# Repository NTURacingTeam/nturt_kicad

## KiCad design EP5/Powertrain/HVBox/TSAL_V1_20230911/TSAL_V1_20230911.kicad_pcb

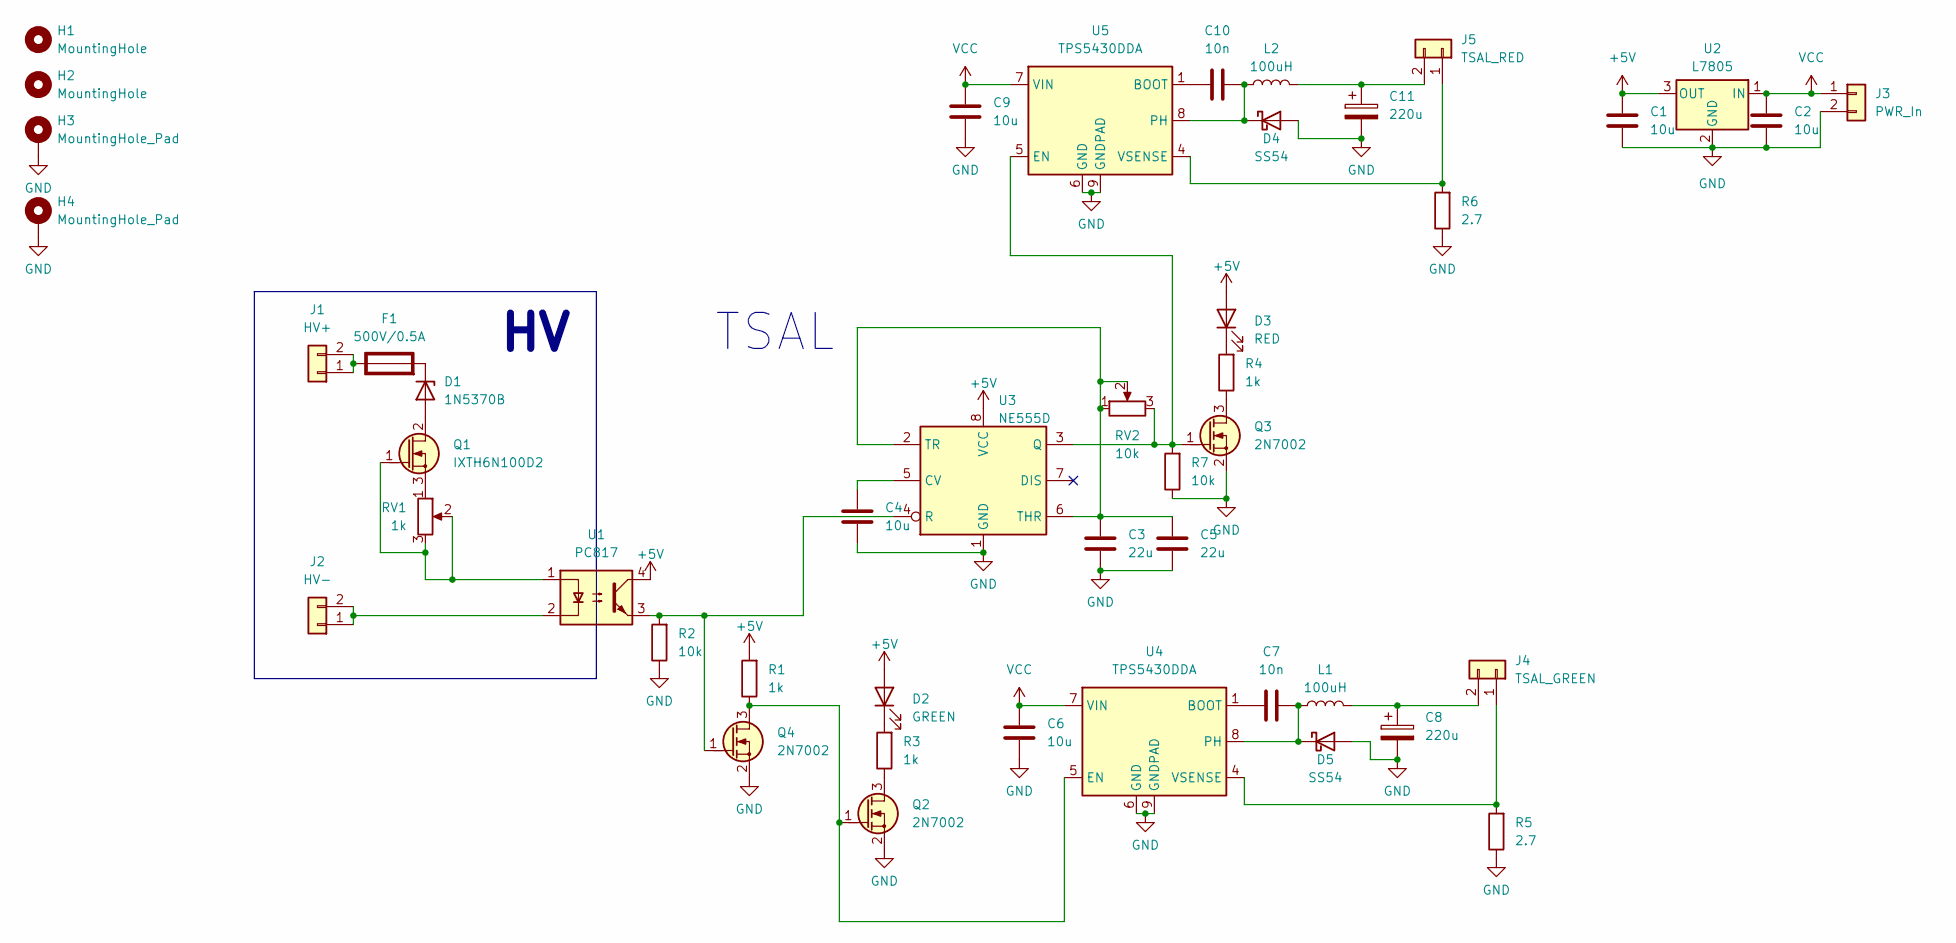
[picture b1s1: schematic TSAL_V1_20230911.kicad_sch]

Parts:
C1, C2, C4, C6, C9: 10u; C_0805_2012Metric_Pad1.18x1.45mm_HandSolder
C3, C5: 22u; C_0805_2012Metric_Pad1.18x1.45mm_HandSolder
C7, C10: 10n; C_0805_2012Metric_Pad1.18x1.45mm_HandSolder
C8, C11: 220u; CP_Elec_8x10.5
D1: 1N5370B; D_P600_R-6_P15.24mm_Horizontal_Zener
D2: GREEN; LED_0805_2012Metric
D3: RED; LED_0805_2012Metric
D4, D5: SS54; D_SMA
F1: 500V/0.5A; 65600001009; Rating W
H1, H2: MountingHole; MountingHole_4.3mm_M4_DIN965
H3, H4: MountingHole_Pad; MountingHole_4.3mm_M4_DIN965_Pad_TopBottom
J1: HV+; DF33C2P33DSA24
J2: HV-; DF33C2P33DSA24
J3: PWR_In; JST_XH_B2B-XH-A_1x02_P2.50mm_Vertical
J4: TSAL_GREEN; JST_XH_B2B-XH-A_1x02_P2.50mm_Vertical
J5: TSAL_RED; JST_XH_B2B-XH-A_1x02_P2.50mm_Vertical
L1, L2: 100uH; L_Sunlord_MWSA1206S-101
Q1: IXTH6N100D2; TO-247-3_Vertical
Q2, Q3, Q4: 2N7002; SOT-23
R1, R3, R4: 1k; R_0805_2012Metric_Pad1.20x1.40mm_HandSolder
R2, R7: 10k; R_0805_2012Metric_Pad1.20x1.40mm_HandSolder
R5, R6: 2.7; R_2512_6332Metric
RV1: 1k; Potentiometer_Bourns_3386C_Horizontal
RV2: 10k; Potentiometer_Bourns_3386C_Horizontal
U1: PC817; SOP-4_3.8x4.1mm_P2.54mm
U2: L7805; TO-252-2
U3: NE555D; SOIC-8_3.9x4.9mm_P1.27mm
U4, U5: TPS5430DDA; TI_SO-PowerPAD-8_ThermalVias

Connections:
+5V: C1.1, D2.2 (A), D3.2 (A), R1.2, U1.4, U2.3 (OUT), U3.8 (VCC)
GND: C1.2, C2.2, C3.2, C4.2, C5.2, C6.2, C8.2, C9.2, C11.2, D4.2 (A), D5.2 (A), H3.1, H4.1, J3.2, Q2.2 (S), Q3.2 (S), Q4.2 (S), R2.1, R5.1, R6.1, R7.1, U2.2 (GND), U3.1 (GND), U4.6 (GND), U4.9 (GNDPAD), U5.6 (GND), U5.9 (GNDPAD)
unnamed: D1.2 (A), Q1.2 (D)
unnamed: D1.1 (K), F1.2 (-)
unnamed: D2.1 (K), R3.2
unnamed: D3.1 (K), R4.2
unnamed: C10.2, D4.1 (K), L2.1, U5.8 (PH)
unnamed: C7.2, D5.1 (K), L1.1, U4.8 (PH)
unnamed: F1.1 (+), J1.1, J1.2
unnamed: J2.1, J2.2, U1.2
unnamed: J4.1, R5.2, U4.4 (VSENSE)
unnamed: C8.1, J4.2, L1.2
unnamed: J5.1, R6.2, U5.4 (VSENSE)
unnamed: C11.1, J5.2, L2.2
unnamed: Q1.1 (G), RV1.2, RV1.3, U1.1
unnamed: Q1.3 (S), RV1.1
unnamed: Q2.3 (D), R3.1
unnamed: Q2.1 (G), Q4.3 (D), R1.1, U4.5 (EN)
unnamed: Q3.3 (D), R4.1
unnamed: Q3.1 (G), R7.2, RV2.3, U3.3 (Q), U5.5 (EN)
unnamed: Q4.1 (G), R2.2, U1.3, U3.4 (R)
unnamed: C4.1, U3.5 (CV)
unnamed: C3.1, C5.1, RV2.1, RV2.2, U3.2 (TR), U3.6 (THR)
unnamed: C7.1, U4.1 (BOOT)
unnamed: C10.1, U5.1 (BOOT)
VCC: C2.1, C6.1, C9.1, J3.1, U2.1 (IN), U4.7 (VIN), U5.7 (VIN)

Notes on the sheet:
TSAL

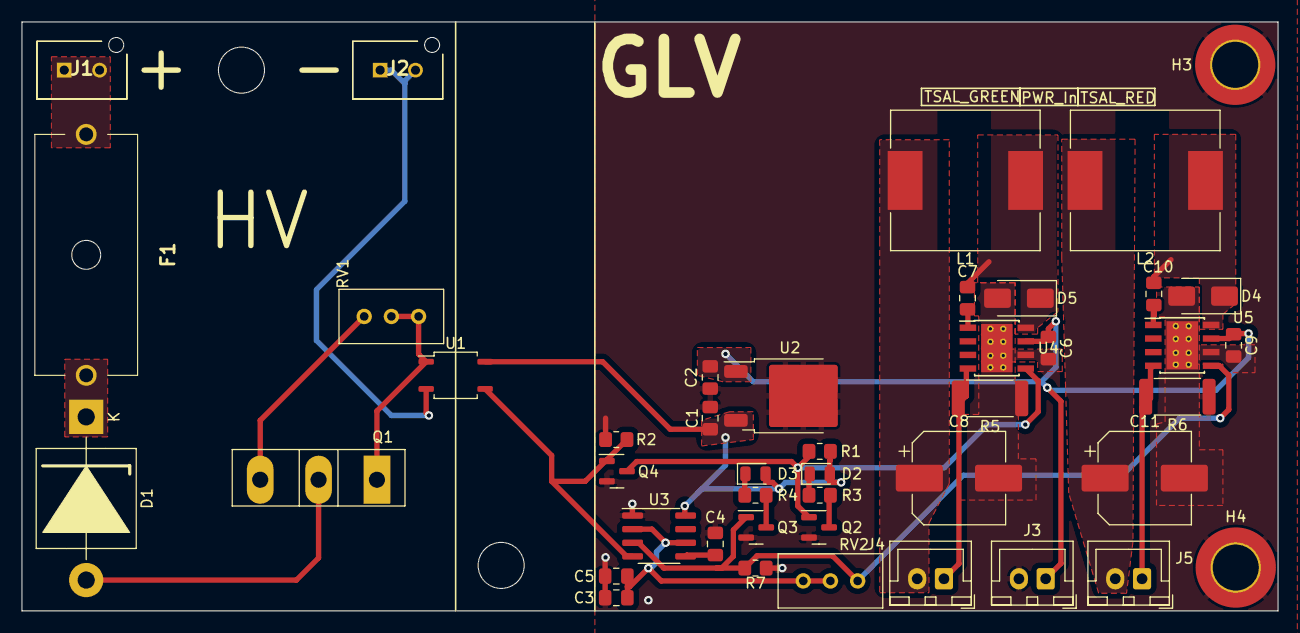
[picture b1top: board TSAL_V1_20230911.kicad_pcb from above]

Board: 2 copper layers, 117.3 x 55.0 mm, 46 parts (0 on the bottom side), 26 nets.

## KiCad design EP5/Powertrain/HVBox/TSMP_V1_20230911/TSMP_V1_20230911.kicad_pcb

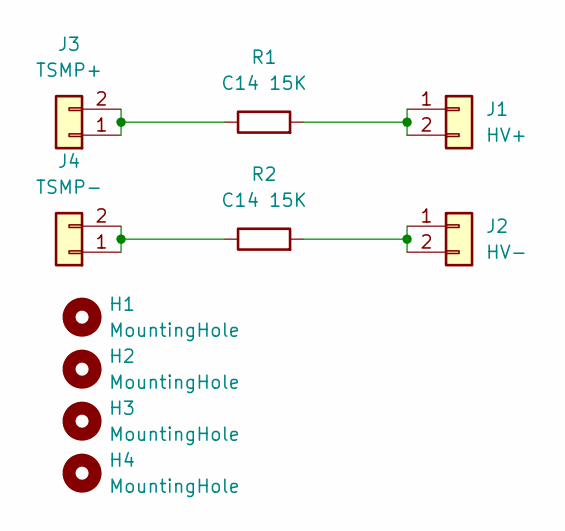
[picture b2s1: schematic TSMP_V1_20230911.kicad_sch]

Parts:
H1, H2, H3, H4: MountingHole; MountingHole_4.3mm_M4_DIN965
J1: HV+; DF33C2P33DSA24
J2: HV-; DF33C2P33DSA24
J3: TSMP+; DF33C2P33DSA24
J4: TSMP-; DF33C2P33DSA24
R1, R2: C14 15K; R_Axial_Power_L60.0mm_W14.0mm_P71.12mm

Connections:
unnamed: J1.1, J1.2, R1.2
unnamed: J2.1, J2.2, R2.2
unnamed: J3.1, J3.2, R1.1
unnamed: J4.1, J4.2, R2.1

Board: 2 copper layers, 10 parts (0 on the bottom side), 4 nets, no tracks yet.

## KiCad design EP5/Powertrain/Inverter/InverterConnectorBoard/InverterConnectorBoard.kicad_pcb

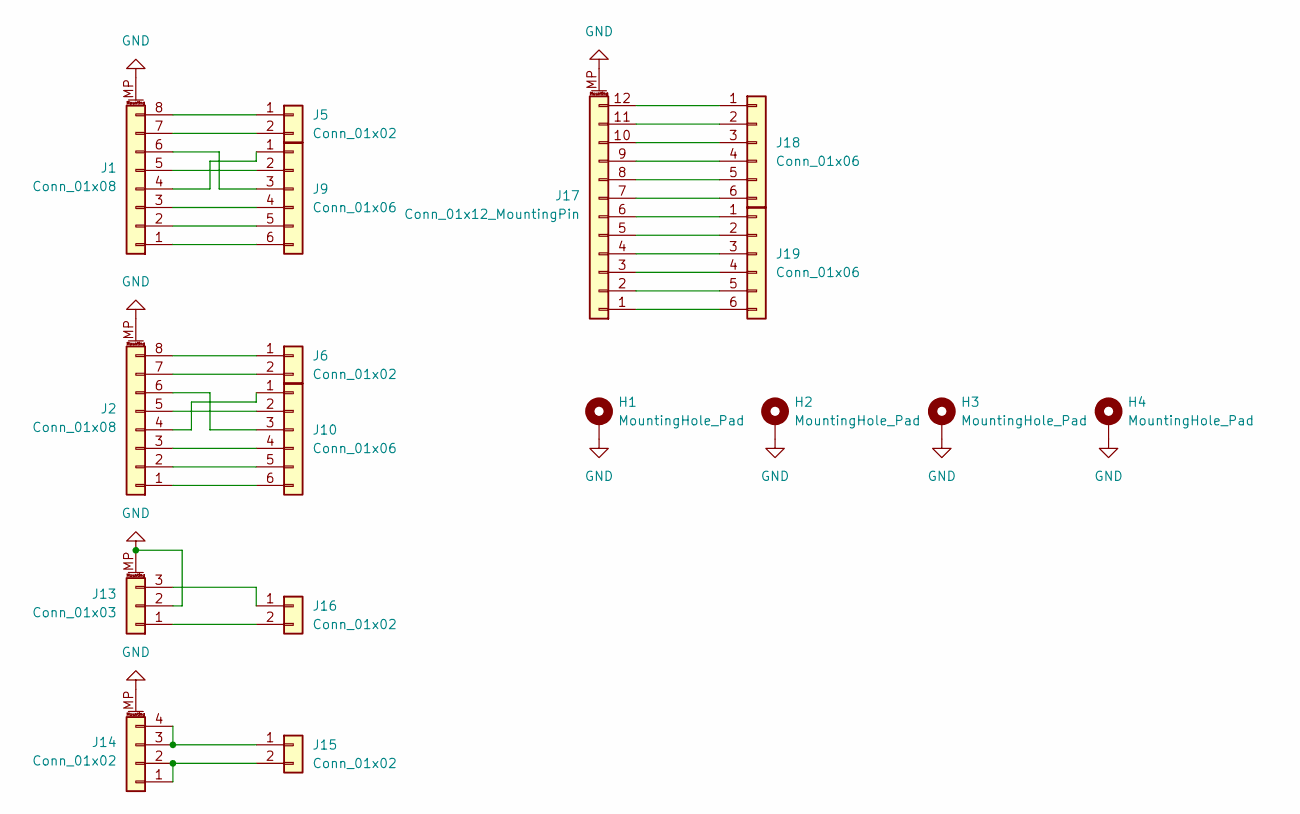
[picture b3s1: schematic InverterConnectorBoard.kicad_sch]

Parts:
H1, H2, H3, H4: MountingHole_Pad; MountingHole_4.3mm_M4_DIN965_Pad_TopBottom
J1, J2: Conn_01x08; M8 8P w Ground
J5, J6, J15, J16: Conn_01x02; JST_XH_B2B-XH-A_1x02_P2.50mm_Vertical
J9, J10, J18, J19: Conn_01x06; JST_XH_B6B-XH-A_1x06_P2.50mm_Vertical
J13: Conn_01x03; M8 3P w Ground
J14: Conn_01x02; M8 2P 4P w Ground
J17: Conn_01x12_MountingPin; M12 12P w Ground

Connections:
GND: H1.1, H2.1, H3.1, H4.1, J1.MP (MountPin), J2.MP (MountPin), J13.2, J13.MP (MountPin), J14.MP (MountPin), J17.MP (MountPin)
unnamed: J1.1, J9.6
unnamed: J1.2, J9.5
unnamed: J1.3, J9.4
unnamed: J1.4, J9.1
unnamed: J1.5, J9.2
unnamed: J1.6, J9.3
unnamed: J1.7, J5.2
unnamed: J1.8, J5.1
unnamed: J2.7, J6.2
unnamed: J2.8, J6.1
unnamed: J2.4, J10.1
unnamed: J2.5, J10.2
unnamed: J2.6, J10.3
unnamed: J2.3, J10.4
unnamed: J2.2, J10.5
unnamed: J2.1, J10.6
unnamed: J13.1, J16.2
unnamed: J13.3, J16.1
unnamed: J14.1, J14.2, J15.2
unnamed: J14.3, J14.4, J15.1
unnamed: J17.1, J19.6
unnamed: J17.2, J19.5
unnamed: J17.3, J19.4
unnamed: J17.4, J19.3
unnamed: J17.5, J19.2
unnamed: J17.6, J19.1
unnamed: J17.7, J18.6
unnamed: J17.8, J18.5
unnamed: J17.9, J18.4
unnamed: J17.10, J18.3
unnamed: J17.11, J18.2
unnamed: J17.12, J18.1

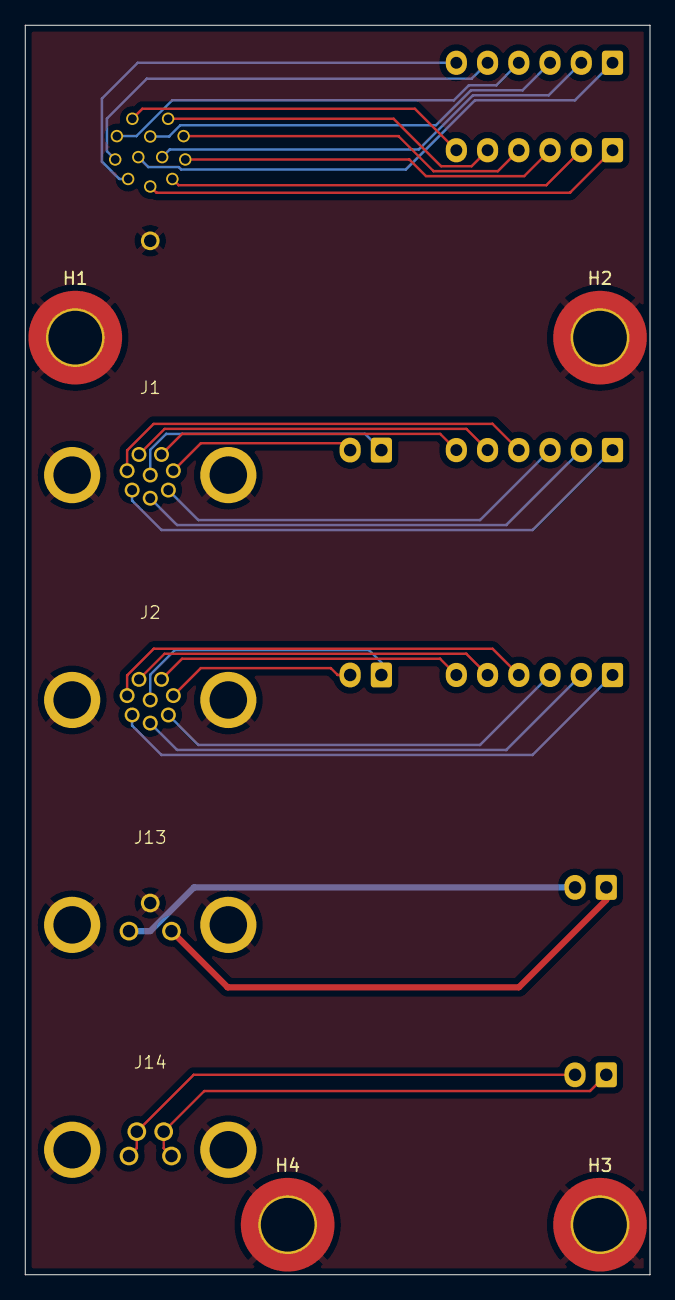
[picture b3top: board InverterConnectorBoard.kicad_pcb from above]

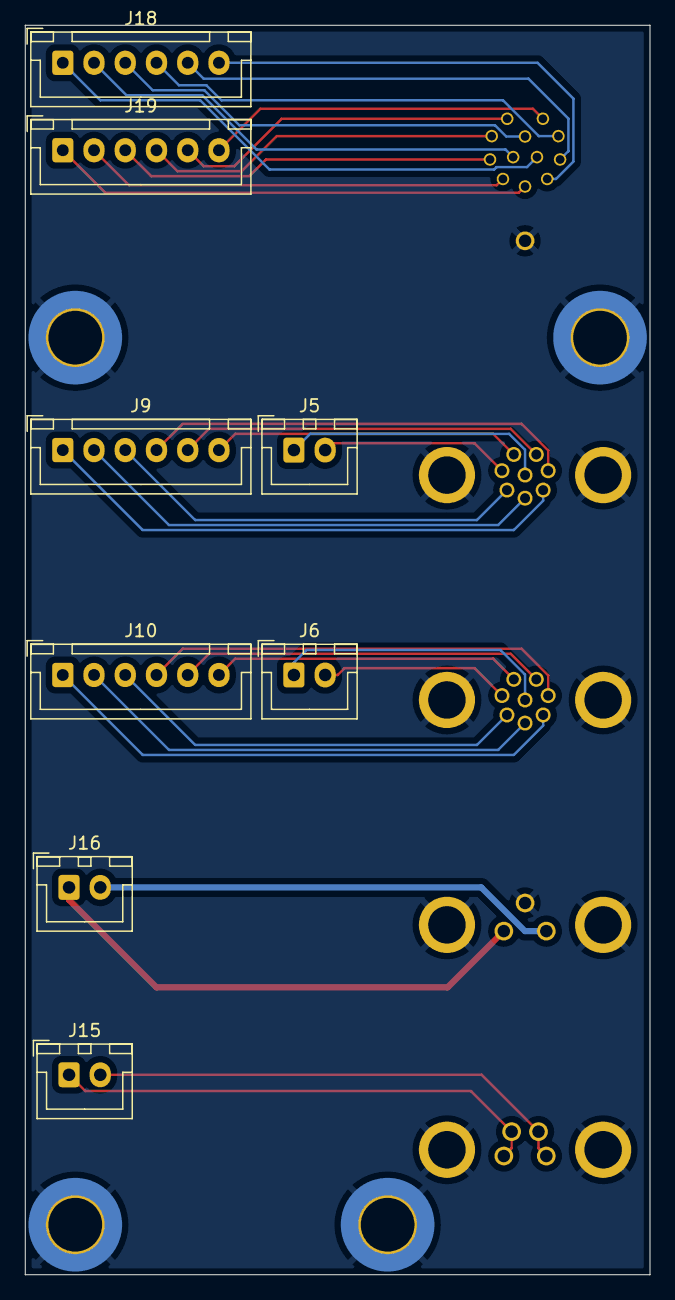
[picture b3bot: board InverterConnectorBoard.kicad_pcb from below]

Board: 2 copper layers, 50.0 x 100.0 mm, 17 parts (8 on the bottom side), 33 nets.

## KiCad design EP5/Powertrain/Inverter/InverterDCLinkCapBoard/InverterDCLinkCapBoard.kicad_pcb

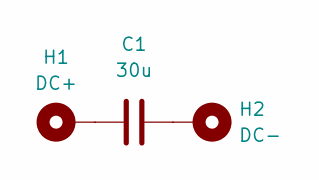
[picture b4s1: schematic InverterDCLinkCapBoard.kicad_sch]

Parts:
C1: 30u; C4AQ-M_WJ
H1: DC+; MountingHole_5.5mm_Pad_Via
H2: DC-; MountingHole_5.5mm_Pad_Via

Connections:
unnamed: C1.1, H1.1
unnamed: C1.2, H2.1

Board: 2 copper layers, 3 parts (0 on the bottom side), 2 nets, no tracks yet.

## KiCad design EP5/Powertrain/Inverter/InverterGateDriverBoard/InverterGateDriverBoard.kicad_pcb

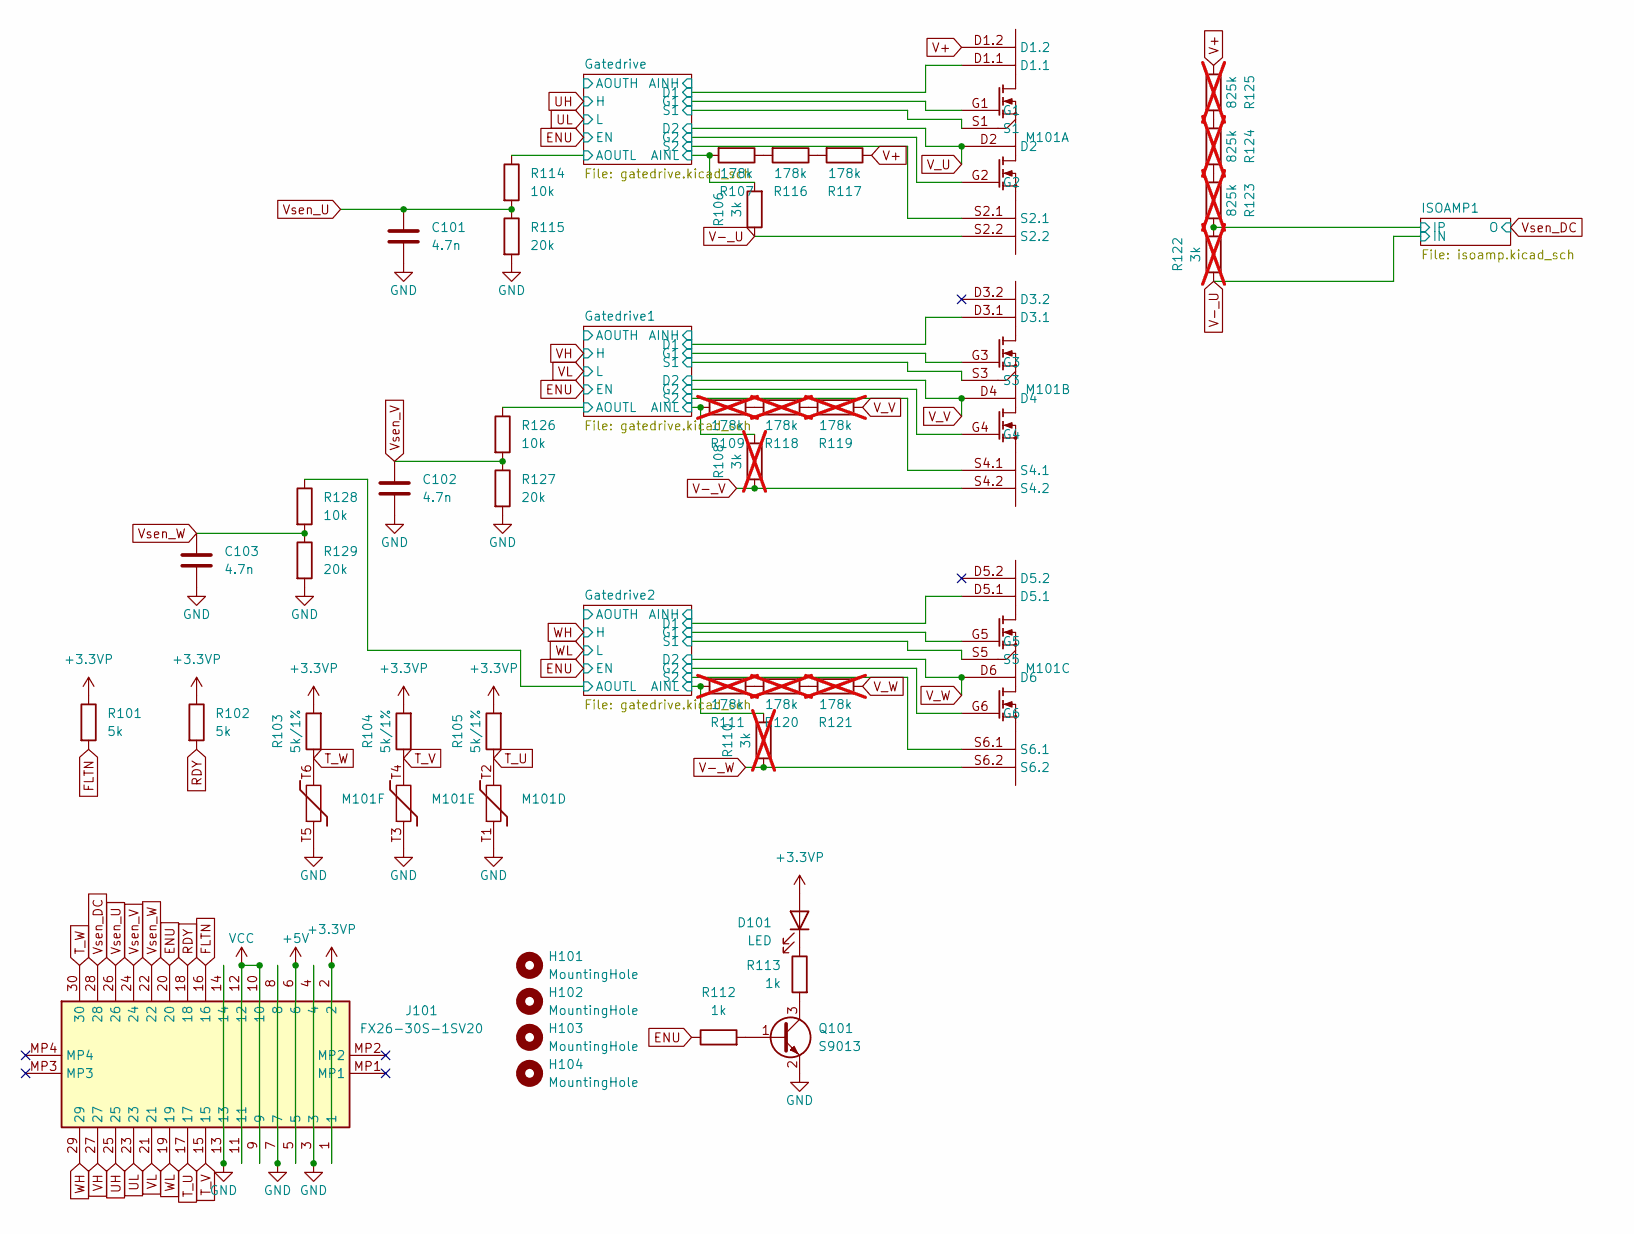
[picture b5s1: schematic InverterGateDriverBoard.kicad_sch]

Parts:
C101, C102, C103: 4.7n; C_0603_1608Metric
D101: LED; LED_0603_1608Metric
H101, H102, H103, H104: MountingHole; MountingHole_4mm
J101: FX26-30S-1SV20; FX2630S1SV20; Mouser Part Number 798-FX2630S1SV20
M101: InverterSiCModule
Q101: S9013; SOT-23-3
R101, R102: 5k; R_0603_1608Metric
R103, R104, R105: 5k/1%; R_0603_1608Metric
R106: 3k; R_1206_3216Metric
R107, R116, R117: 178k; R_1206_3216Metric
R108, R110, R122: 3k; R_1206_3216Metric; not fitted
R109, R111, R118, R119, R120, R121: 178k; R_1206_3216Metric; not fitted
R112, R113: 1k; R_0603_1608Metric
R114, R126, R128: 10k; R_0603_1608Metric
R115, R127, R129: 20k; R_0603_1608Metric
R123, R124, R125: 825k; R_1206_3216Metric; not fitted

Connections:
+3.3VP: D101.2 (A), J101.1, J101.2, R101.1, R102.1, R103.2, R104.2, R105.2; also elsewhere on the board
+5V: J101.5, J101.6; also elsewhere on the board
/Gatedrive1/AINL: R108.2, R109.2; also elsewhere on the board
/Gatedrive1/AOUTL: R126.1; also elsewhere on the board
/Gatedrive1/D1: M101.D3.1; also elsewhere on the board
/Gatedrive1/G1: M101.G3; also elsewhere on the board
/Gatedrive1/G2: M101.G4; also elsewhere on the board
/Gatedrive1/S1: M101.S3; also elsewhere on the board
/Gatedrive1/S2: M101.S4.1; also elsewhere on the board
/Gatedrive2/AINL: R110.2, R111.2; also elsewhere on the board
/Gatedrive2/AOUTL: R128.1; also elsewhere on the board
/Gatedrive2/D1: M101.D5.1; also elsewhere on the board
/Gatedrive2/G1: M101.G5; also elsewhere on the board
/Gatedrive2/G2: M101.G6; also elsewhere on the board
/Gatedrive2/S1: M101.S5; also elsewhere on the board
/Gatedrive2/S2: M101.S6.1; also elsewhere on the board
/Gatedrive/AINL: R106.2, R107.2; also elsewhere on the board
/Gatedrive/AOUTL: R114.1; also elsewhere on the board
/Gatedrive/D1: M101.D1.1; also elsewhere on the board
/Gatedrive/G1: M101.G1; also elsewhere on the board
/Gatedrive/G2: M101.G2; also elsewhere on the board
/Gatedrive/S1: M101.S1; also elsewhere on the board
/Gatedrive/S2: M101.S2.1; also elsewhere on the board
/ISOAMP1/IP: R122.2, R123.2; also elsewhere on the board
ENU: J101.20, R112.1; also elsewhere on the board
FLTN: J101.16, R101.2; also elsewhere on the board
GND: C101.1, C102.1, C103.1, J101.3, J101.4, J101.7, J101.8, J101.13, J101.14, M101.T1, M101.T3, M101.T5, Q101.2 (E), R115.2, R127.2, R129.2; also elsewhere on the board
unnamed: D101.1 (K), R113.1
unnamed: Q101.1 (B), R112.2
unnamed: Q101.3 (C), R113.2
unnamed: R107.1, R116.2
unnamed: R109.1, R118.2
unnamed: R111.1, R120.2
unnamed: R116.1, R117.2
unnamed: R118.1, R119.2
unnamed: R120.1, R121.2
unnamed: R123.1, R124.2
unnamed: R124.1, R125.2
RDY: J101.18, R102.2; also elsewhere on the board
T_U: J101.17, M101.T2, R105.1
T_V: J101.15, M101.T4, R104.1
T_W: J101.30, M101.T6, R103.1
UH: J101.25; also elsewhere on the board
UL: J101.23; also elsewhere on the board
V+: M101.D1.2, R117.1, R125.1
V-_U: M101.S2.2, R106.1, R122.1; also elsewhere on the board
V-_V: M101.S4.2, R108.1
V-_W: M101.S6.2, R110.1
VCC: J101.9, J101.10, J101.11, J101.12; also elsewhere on the board
VH: J101.27; also elsewhere on the board
VL: J101.21; also elsewhere on the board
V_U: M101.D2; also elsewhere on the board
V_V: M101.D4, R119.1; also elsewhere on the board
V_W: M101.D6, R121.1; also elsewhere on the board
Vsen_DC: J101.28; also elsewhere on the board
Vsen_U: C101.2, J101.26, R114.2, R115.1
Vsen_V: C102.2, J101.24, R126.2, R127.1
Vsen_W: C103.2, J101.22, R128.2, R129.1
WH: J101.29; also elsewhere on the board
WL: J101.19; also elsewhere on the board

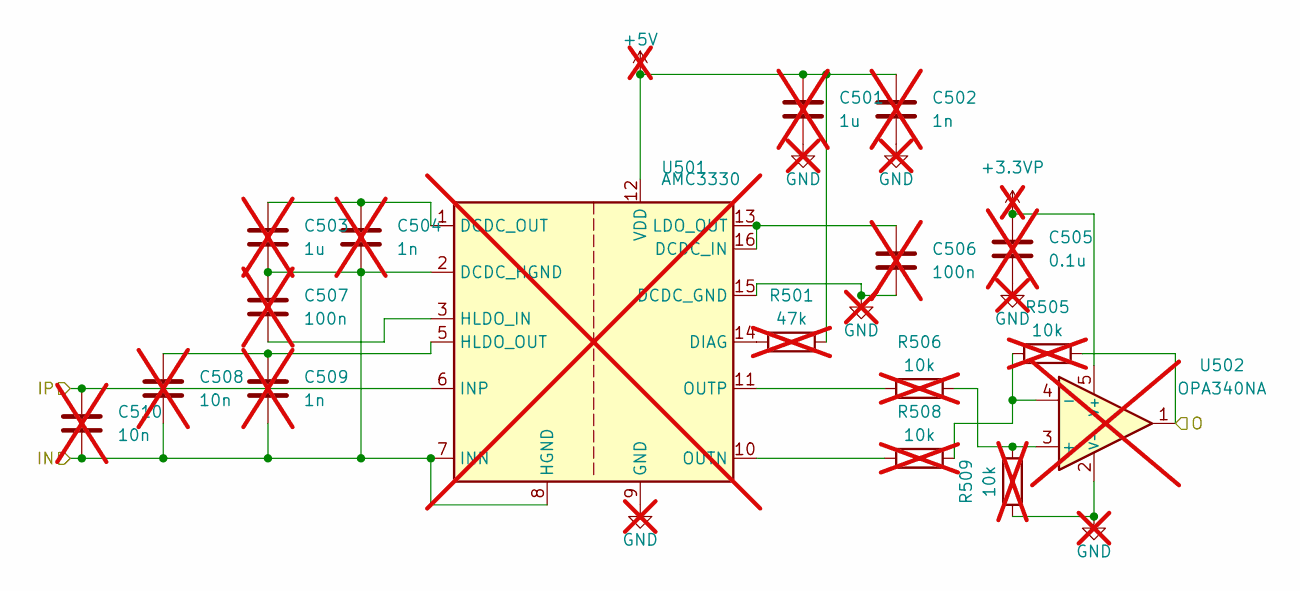
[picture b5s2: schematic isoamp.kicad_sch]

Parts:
C501: 1u; C_1206_3216Metric; not fitted
C502, C509: 1n; C_1206_3216Metric; not fitted
C503: 1u; C_0603_1608Metric; not fitted
C504: 1n; C_0603_1608Metric; not fitted
C505: 0.1u; C_0603_1608Metric; not fitted
C506, C507: 100n; C_0603_1608Metric; not fitted
C508: 10n; C_1206_3216Metric; not fitted
C510: 10n; C_0603_1608Metric; not fitted
R501: 47k; R_0603_1608Metric; not fitted
R505, R506, R508, R509: 10k; R_0603_1608Metric; not fitted
U501: AMC3330; SOIC-16W_7.5x10.3mm_P1.27mm; not fitted
U502: OPA340NA; SOT-23-5; not fitted

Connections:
+3.3VP: C505.2, U502.5 (V+); also elsewhere on the board
+5V: C501.2, C502.2, R501.2, U501.12 (VDD); also elsewhere on the board
/ISOAMP1/IP: C510.2, U501.6 (INP); also elsewhere on the board
GND: C501.1, C502.1, C505.1, C506.1, R509.1, U501.9 (GND), U501.15 (DCDC_GND), U502.2 (V-); also elsewhere on the board
unnamed: C506.2, U501.13 (LDO_OUT), U501.16 (DCDC_IN)
unnamed: C503.2, C504.2, U501.1 (DCDC_OUT)
unnamed: R501.1, U501.14 (DIAG)
unnamed: C507.1, U501.3 (HLDO_IN)
unnamed: C508.2, C509.2, U501.5 (HLDO_OUT)
unnamed: R508.1, U501.10 (OUTN)
unnamed: R506.1, U501.11 (OUTP)
unnamed: R506.2, R509.2, U502.3 (+)
unnamed: R505.1, R508.2, U502.4 (-)
V-_U: C503.1, C504.1, C507.2, C508.1, C509.1, C510.1, U501.2 (DCDC_HGND), U501.7 (INN), U501.8 (HGND); also elsewhere on the board
Vsen_DC: R505.2, U502.1; also elsewhere on the board

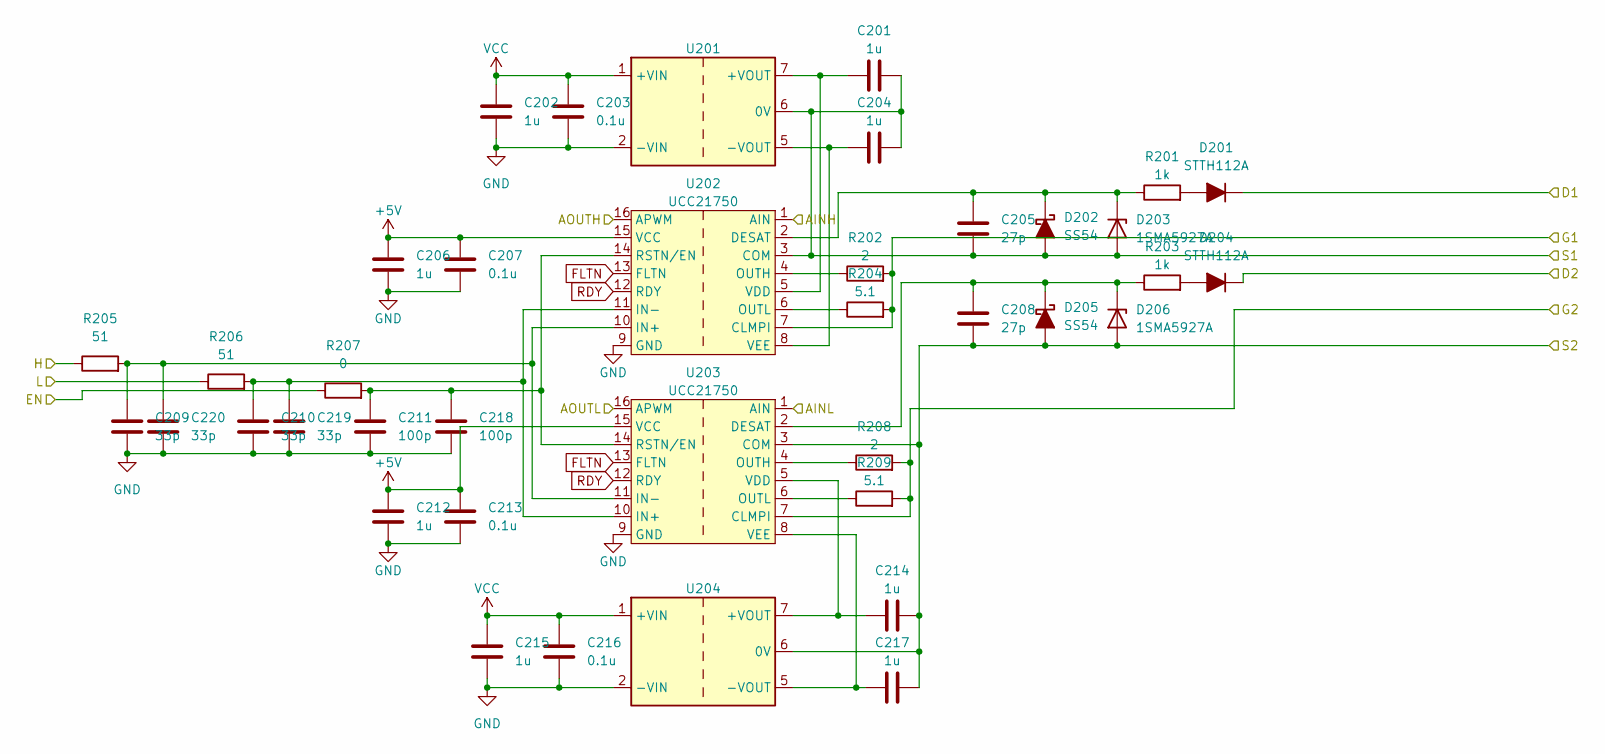
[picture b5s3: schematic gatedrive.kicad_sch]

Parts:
C201, C214: 1u; C_1206_3216Metric
C202, C204, C206, C212, C215, C217: 1u; C_0603_1608Metric
C203, C207, C213, C216: 0.1u; C_0603_1608Metric
C205, C208: 27p; C_0603_1608Metric
C209, C210, C219, C220: 33p; C_0603_1608Metric
C211, C218: 100p; C_0603_1608Metric
D201, D204: STTH112A; D_SMA
D202, D205: SS54; D_SMA
D203, D206: 1SMA5927A; D_SMA
R201, R203: 1k; R_1206_3216Metric
R202, R208: 2; R_2512_6332Metric
R204, R209: 5.1; R_2512_6332Metric
R205, R206: 51; R_0603_1608Metric
R207: 0; R_0603_1608Metric
U201, U204: Converter_DCDC_Murata_MGJ2DxxxxxxSC_THT
U202, U203: UCC21750; SOIC-16W_7.5x10.3mm_P1.27mm

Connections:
+5V: C206.2, C207.2, C212.2, C213.2, U202.15 (VCC), U203.15 (VCC); also elsewhere on the board
/Gatedrive/AINH: U202.1 (AIN)
/Gatedrive/AINL: U203.1 (AIN); also elsewhere on the board
/Gatedrive/AOUTH: U202.16 (APWM)
/Gatedrive/AOUTL: U203.16 (APWM); also elsewhere on the board
/Gatedrive/D1: D201.1 (K); also elsewhere on the board
/Gatedrive/G1: R202.2, R204.2, U202.7 (CLMPI); also elsewhere on the board
/Gatedrive/G2: R208.2, R209.2, U203.7 (CLMPI); also elsewhere on the board
/Gatedrive/S1: C201.1, C204.1, C205.1, D202.2 (A), D203.2 (A), U201.6 (0V), U202.3 (COM); also elsewhere on the board
/Gatedrive/S2: C208.1, C214.1, C217.2, D205.2 (A), D206.2 (A), U203.3 (COM), U204.6 (0V); also elsewhere on the board
ENU: R207.1; also elsewhere on the board
FLTN: U202.13 (FLTN), U203.13 (FLTN); also elsewhere on the board
GND: C202.1, C203.1, C206.1, C207.1, C209.1, C210.1, C211.1, C212.1, C213.1, C215.1, C216.1, C218.1, C219.1, C220.1, U201.2 (-VIN), U202.9 (GND), U203.9 (GND), U204.2 (-VIN); also elsewhere on the board
unnamed: D201.2 (A), R201.2
unnamed: C205.2, D202.1 (K), D203.1 (K), R201.1, U202.2 (DESAT)
unnamed: D204.2 (A), R203.2
unnamed: C208.2, D205.1 (K), D206.1 (K), R203.1, U203.2 (DESAT)
unnamed: C201.2, U201.7 (+VOUT), U202.5 (VDD)
unnamed: C204.2, U201.5 (-VOUT), U202.8 (VEE)
unnamed: C209.2, C220.2, R205.2, U202.10 (IN+), U203.11 (IN-)
unnamed: C210.2, C219.2, R206.2, U202.11 (IN-), U203.10 (IN+)
unnamed: R202.1, U202.4 (OUTH)
unnamed: R204.1, U202.6 (OUTL)
unnamed: C211.2, C218.2, R207.2, U202.14 (RSTN/EN), U203.14 (RSTN/EN)
unnamed: R208.1, U203.4 (OUTH)
unnamed: R209.1, U203.6 (OUTL)
unnamed: C214.2, U203.5 (VDD), U204.7 (+VOUT)
unnamed: C217.1, U203.8 (VEE), U204.5 (-VOUT)
RDY: U202.12 (RDY), U203.12 (RDY); also elsewhere on the board
UH: R205.1; also elsewhere on the board
UL: R206.1; also elsewhere on the board
VCC: C202.2, C203.2, C215.2, C216.2, U201.1 (+VIN), U204.1 (+VIN); also elsewhere on the board
V_U: D204.1 (K); also elsewhere on the board

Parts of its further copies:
C301, C314, C401, C414: 1u; C_1206_3216Metric
C302, C304, C306, C312, C315, C317, C402, C404, C406, C412, C415, C417: 1u; C_0603_1608Metric
C303, C307, C313, C316, C403, C407, C413, C416: 0.1u; C_0603_1608Metric
C305, C308, C405, C408: 27p; C_0603_1608Metric
C309, C310, C319, C320, C409, C410, C419, C420: 33p; C_0603_1608Metric
C311, C318, C411, C418: 100p; C_0603_1608Metric
D301, D304, D401, D404: STTH112A; D_SMA
D302, D305, D402, D405: SS54; D_SMA
D303, D306, D403, D406: 1SMA5927A; D_SMA
R301, R303, R401, R403: 1k; R_1206_3216Metric
R302, R308, R402, R408: 2; R_2512_6332Metric
R304, R309, R404, R409: 5.1; R_2512_6332Metric
R305, R306, R405, R406: 51; R_0603_1608Metric
R307, R407: 0; R_0603_1608Metric
U301, U304, U401, U404: Converter_DCDC_Murata_MGJ2DxxxxxxSC_THT
U302, U303, U402, U403: UCC21750; SOIC-16W_7.5x10.3mm_P1.27mm

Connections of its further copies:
+5V: C306.2, C307.2, C312.2, C313.2, C406.2, C407.2, C412.2, C413.2, U302.15 (VCC), U303.15 (VCC), U402.15 (VCC), U403.15 (VCC); also elsewhere on the board
/Gatedrive1/AINH: U302.1 (AIN)
/Gatedrive1/AINL: U303.1 (AIN); also elsewhere on the board
/Gatedrive1/AOUTH: U302.16 (APWM)
/Gatedrive1/AOUTL: U303.16 (APWM); also elsewhere on the board
/Gatedrive1/D1: D301.1 (K); also elsewhere on the board
/Gatedrive1/G1: R302.2, R304.2, U302.7 (CLMPI); also elsewhere on the board
/Gatedrive1/G2: R308.2, R309.2, U303.7 (CLMPI); also elsewhere on the board
/Gatedrive1/S1: C301.1, C304.1, C305.1, D302.2 (A), D303.2 (A), U301.6 (0V), U302.3 (COM); also elsewhere on the board
/Gatedrive1/S2: C308.1, C314.1, C317.2, D305.2 (A), D306.2 (A), U303.3 (COM), U304.6 (0V); also elsewhere on the board
/Gatedrive2/AINH: U402.1 (AIN)
/Gatedrive2/AINL: U403.1 (AIN); also elsewhere on the board
/Gatedrive2/AOUTH: U402.16 (APWM)
/Gatedrive2/AOUTL: U403.16 (APWM); also elsewhere on the board
/Gatedrive2/D1: D401.1 (K); also elsewhere on the board
/Gatedrive2/G1: R402.2, R404.2, U402.7 (CLMPI); also elsewhere on the board
/Gatedrive2/G2: R408.2, R409.2, U403.7 (CLMPI); also elsewhere on the board
/Gatedrive2/S1: C401.1, C404.1, C405.1, D402.2 (A), D403.2 (A), U401.6 (0V), U402.3 (COM); also elsewhere on the board
/Gatedrive2/S2: C408.1, C414.1, C417.2, D405.2 (A), D406.2 (A), U403.3 (COM), U404.6 (0V); also elsewhere on the board
ENU: R307.1, R407.1; also elsewhere on the board
FLTN: U302.13 (FLTN), U303.13 (FLTN), U402.13 (FLTN), U403.13 (FLTN); also elsewhere on the board
GND: C302.1, C303.1, C306.1, C307.1, C309.1, C310.1, C311.1, C312.1, C313.1, C315.1, C316.1, C318.1, C319.1, C320.1, C402.1, C403.1, C406.1, C407.1, C409.1, C410.1, C411.1, C412.1, C413.1, C415.1, C416.1, C418.1, C419.1, C420.1, U301.2 (-VIN), U302.9 (GND), U303.9 (GND), U304.2 (-VIN), U401.2 (-VIN), U402.9 (GND), U403.9 (GND), U404.2 (-VIN); also elsewhere on the board
unnamed: D301.2 (A), R301.2
unnamed: C305.2, D302.1 (K), D303.1 (K), R301.1, U302.2 (DESAT)
unnamed: D304.2 (A), R303.2
unnamed: C308.2, D305.1 (K), D306.1 (K), R303.1, U303.2 (DESAT)
unnamed: D401.2 (A), R401.2
unnamed: C405.2, D402.1 (K), D403.1 (K), R401.1, U402.2 (DESAT)
unnamed: D404.2 (A), R403.2
unnamed: C408.2, D405.1 (K), D406.1 (K), R403.1, U403.2 (DESAT)
unnamed: C301.2, U301.7 (+VOUT), U302.5 (VDD)
unnamed: C304.2, U301.5 (-VOUT), U302.8 (VEE)
unnamed: C309.2, C320.2, R305.2, U302.10 (IN+), U303.11 (IN-)
unnamed: C310.2, C319.2, R306.2, U302.11 (IN-), U303.10 (IN+)
unnamed: R302.1, U302.4 (OUTH)
unnamed: R304.1, U302.6 (OUTL)
unnamed: C311.2, C318.2, R307.2, U302.14 (RSTN/EN), U303.14 (RSTN/EN)
unnamed: R308.1, U303.4 (OUTH)
unnamed: R309.1, U303.6 (OUTL)
unnamed: C314.2, U303.5 (VDD), U304.7 (+VOUT)
unnamed: C317.1, U303.8 (VEE), U304.5 (-VOUT)
unnamed: C401.2, U401.7 (+VOUT), U402.5 (VDD)
unnamed: C404.2, U401.5 (-VOUT), U402.8 (VEE)
unnamed: C409.2, C420.2, R405.2, U402.10 (IN+), U403.11 (IN-)
unnamed: C410.2, C419.2, R406.2, U402.11 (IN-), U403.10 (IN+)
unnamed: R402.1, U402.4 (OUTH)
unnamed: R404.1, U402.6 (OUTL)
unnamed: C411.2, C418.2, R407.2, U402.14 (RSTN/EN), U403.14 (RSTN/EN)
unnamed: R408.1, U403.4 (OUTH)
unnamed: R409.1, U403.6 (OUTL)
unnamed: C414.2, U403.5 (VDD), U404.7 (+VOUT)
unnamed: C417.1, U403.8 (VEE), U404.5 (-VOUT)
RDY: U302.12 (RDY), U303.12 (RDY), U402.12 (RDY), U403.12 (RDY); also elsewhere on the board
VCC: C302.2, C303.2, C315.2, C316.2, C402.2, C403.2, C415.2, C416.2, U301.1 (+VIN), U304.1 (+VIN), U401.1 (+VIN), U404.1 (+VIN); also elsewhere on the board
VH: R305.1; also elsewhere on the board
VL: R306.1; also elsewhere on the board
V_V: D304.1 (K); also elsewhere on the board
V_W: D404.1 (K); also elsewhere on the board
WH: R405.1; also elsewhere on the board
WL: R406.1; also elsewhere on the board

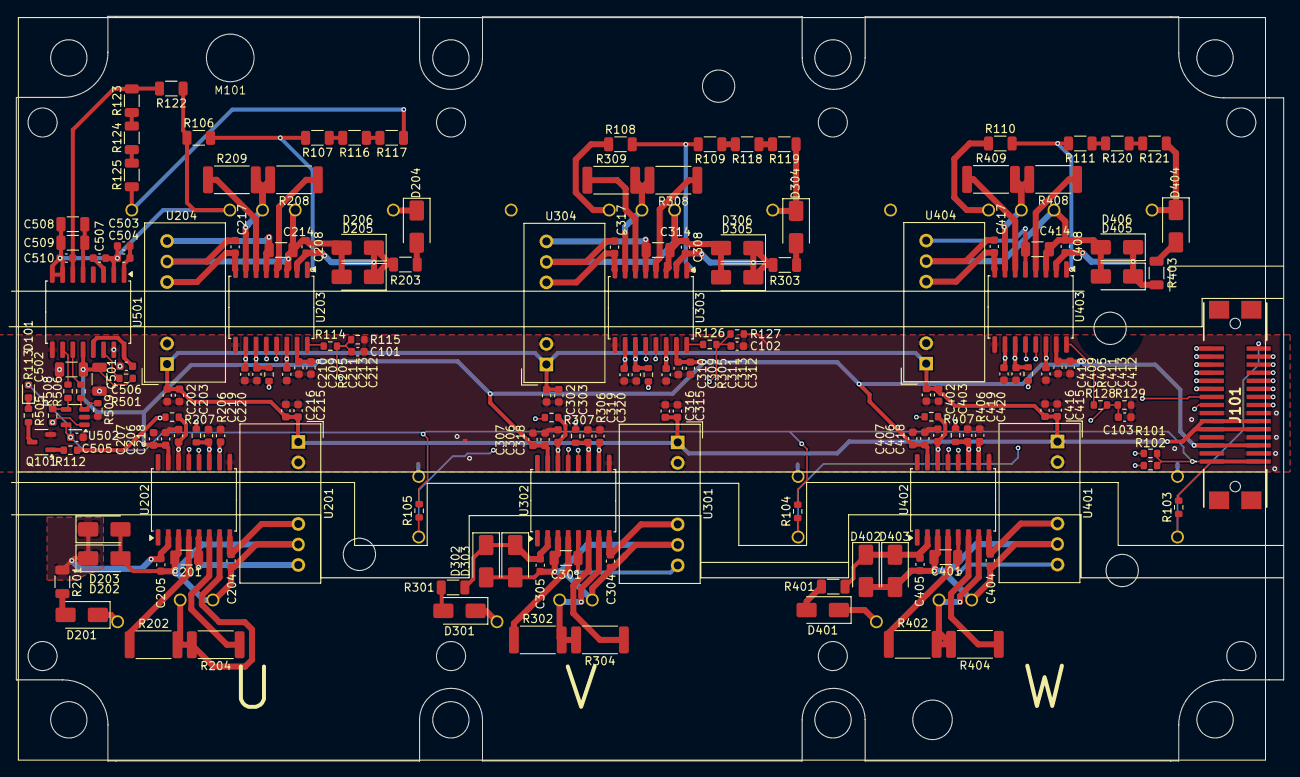
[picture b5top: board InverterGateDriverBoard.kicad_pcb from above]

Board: 4 copper layers, 157.0 x 92.2 mm, 174 parts (0 on the bottom side), 114 nets.
